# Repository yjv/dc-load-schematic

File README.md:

View this project on [CADLAB.io](https://cadlab.io/project/28803). 

# dc-load-schematic

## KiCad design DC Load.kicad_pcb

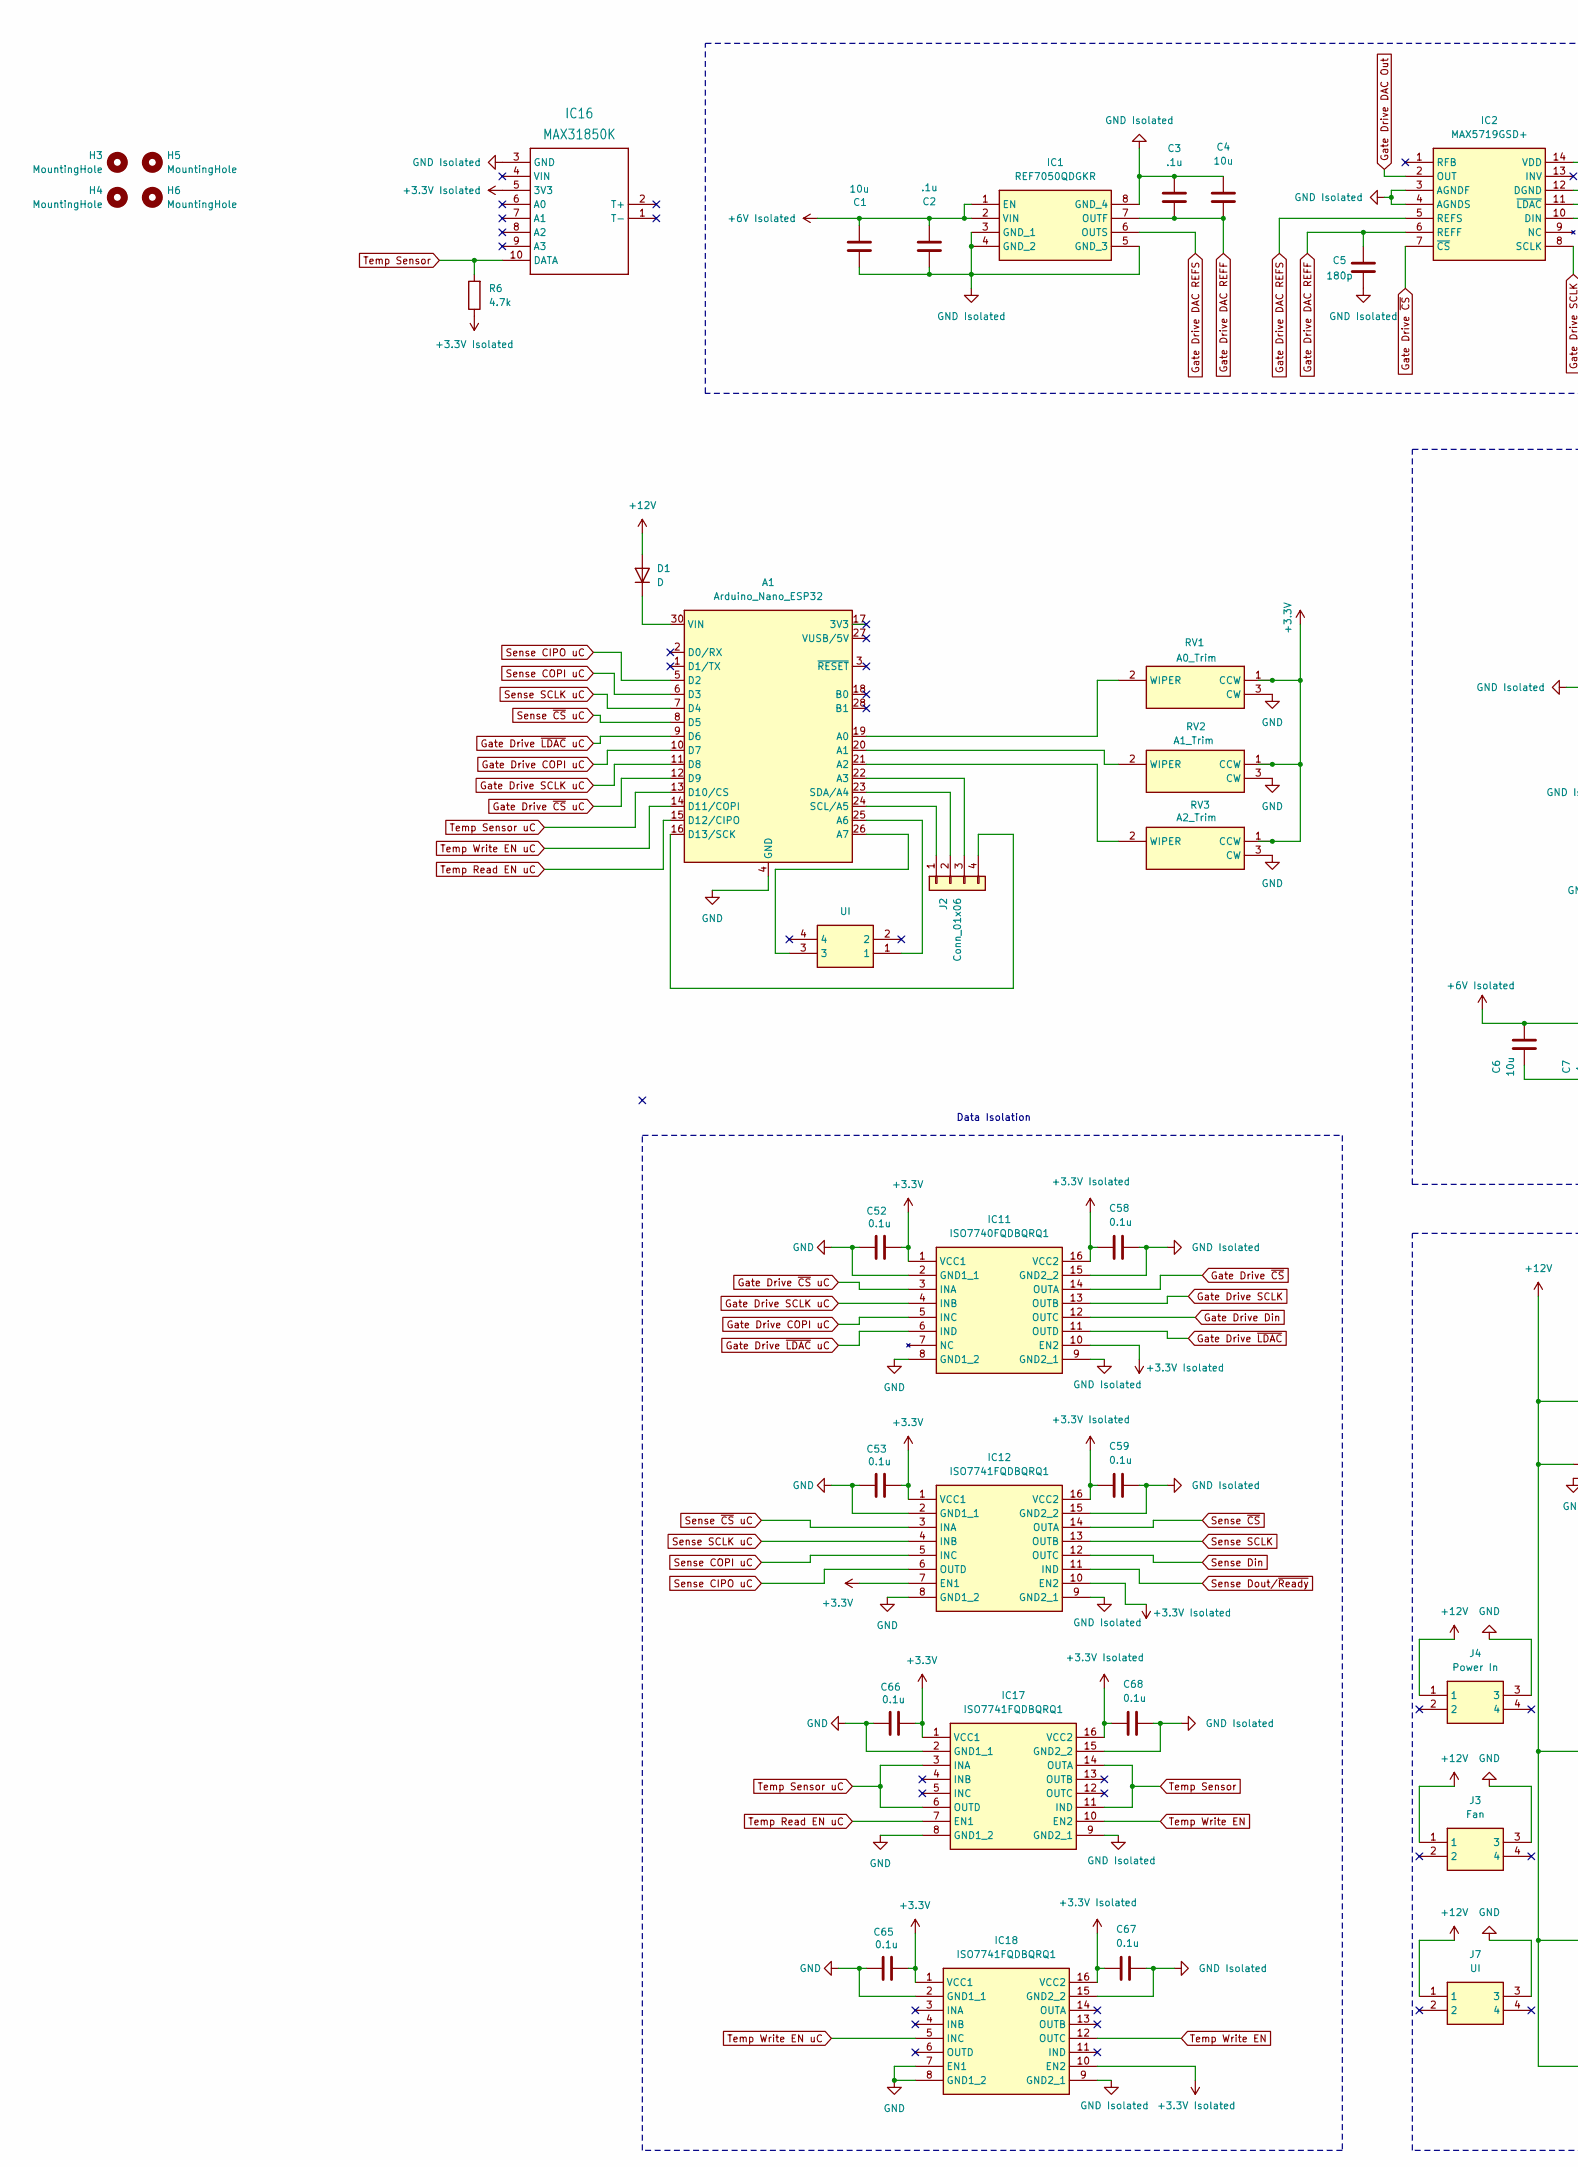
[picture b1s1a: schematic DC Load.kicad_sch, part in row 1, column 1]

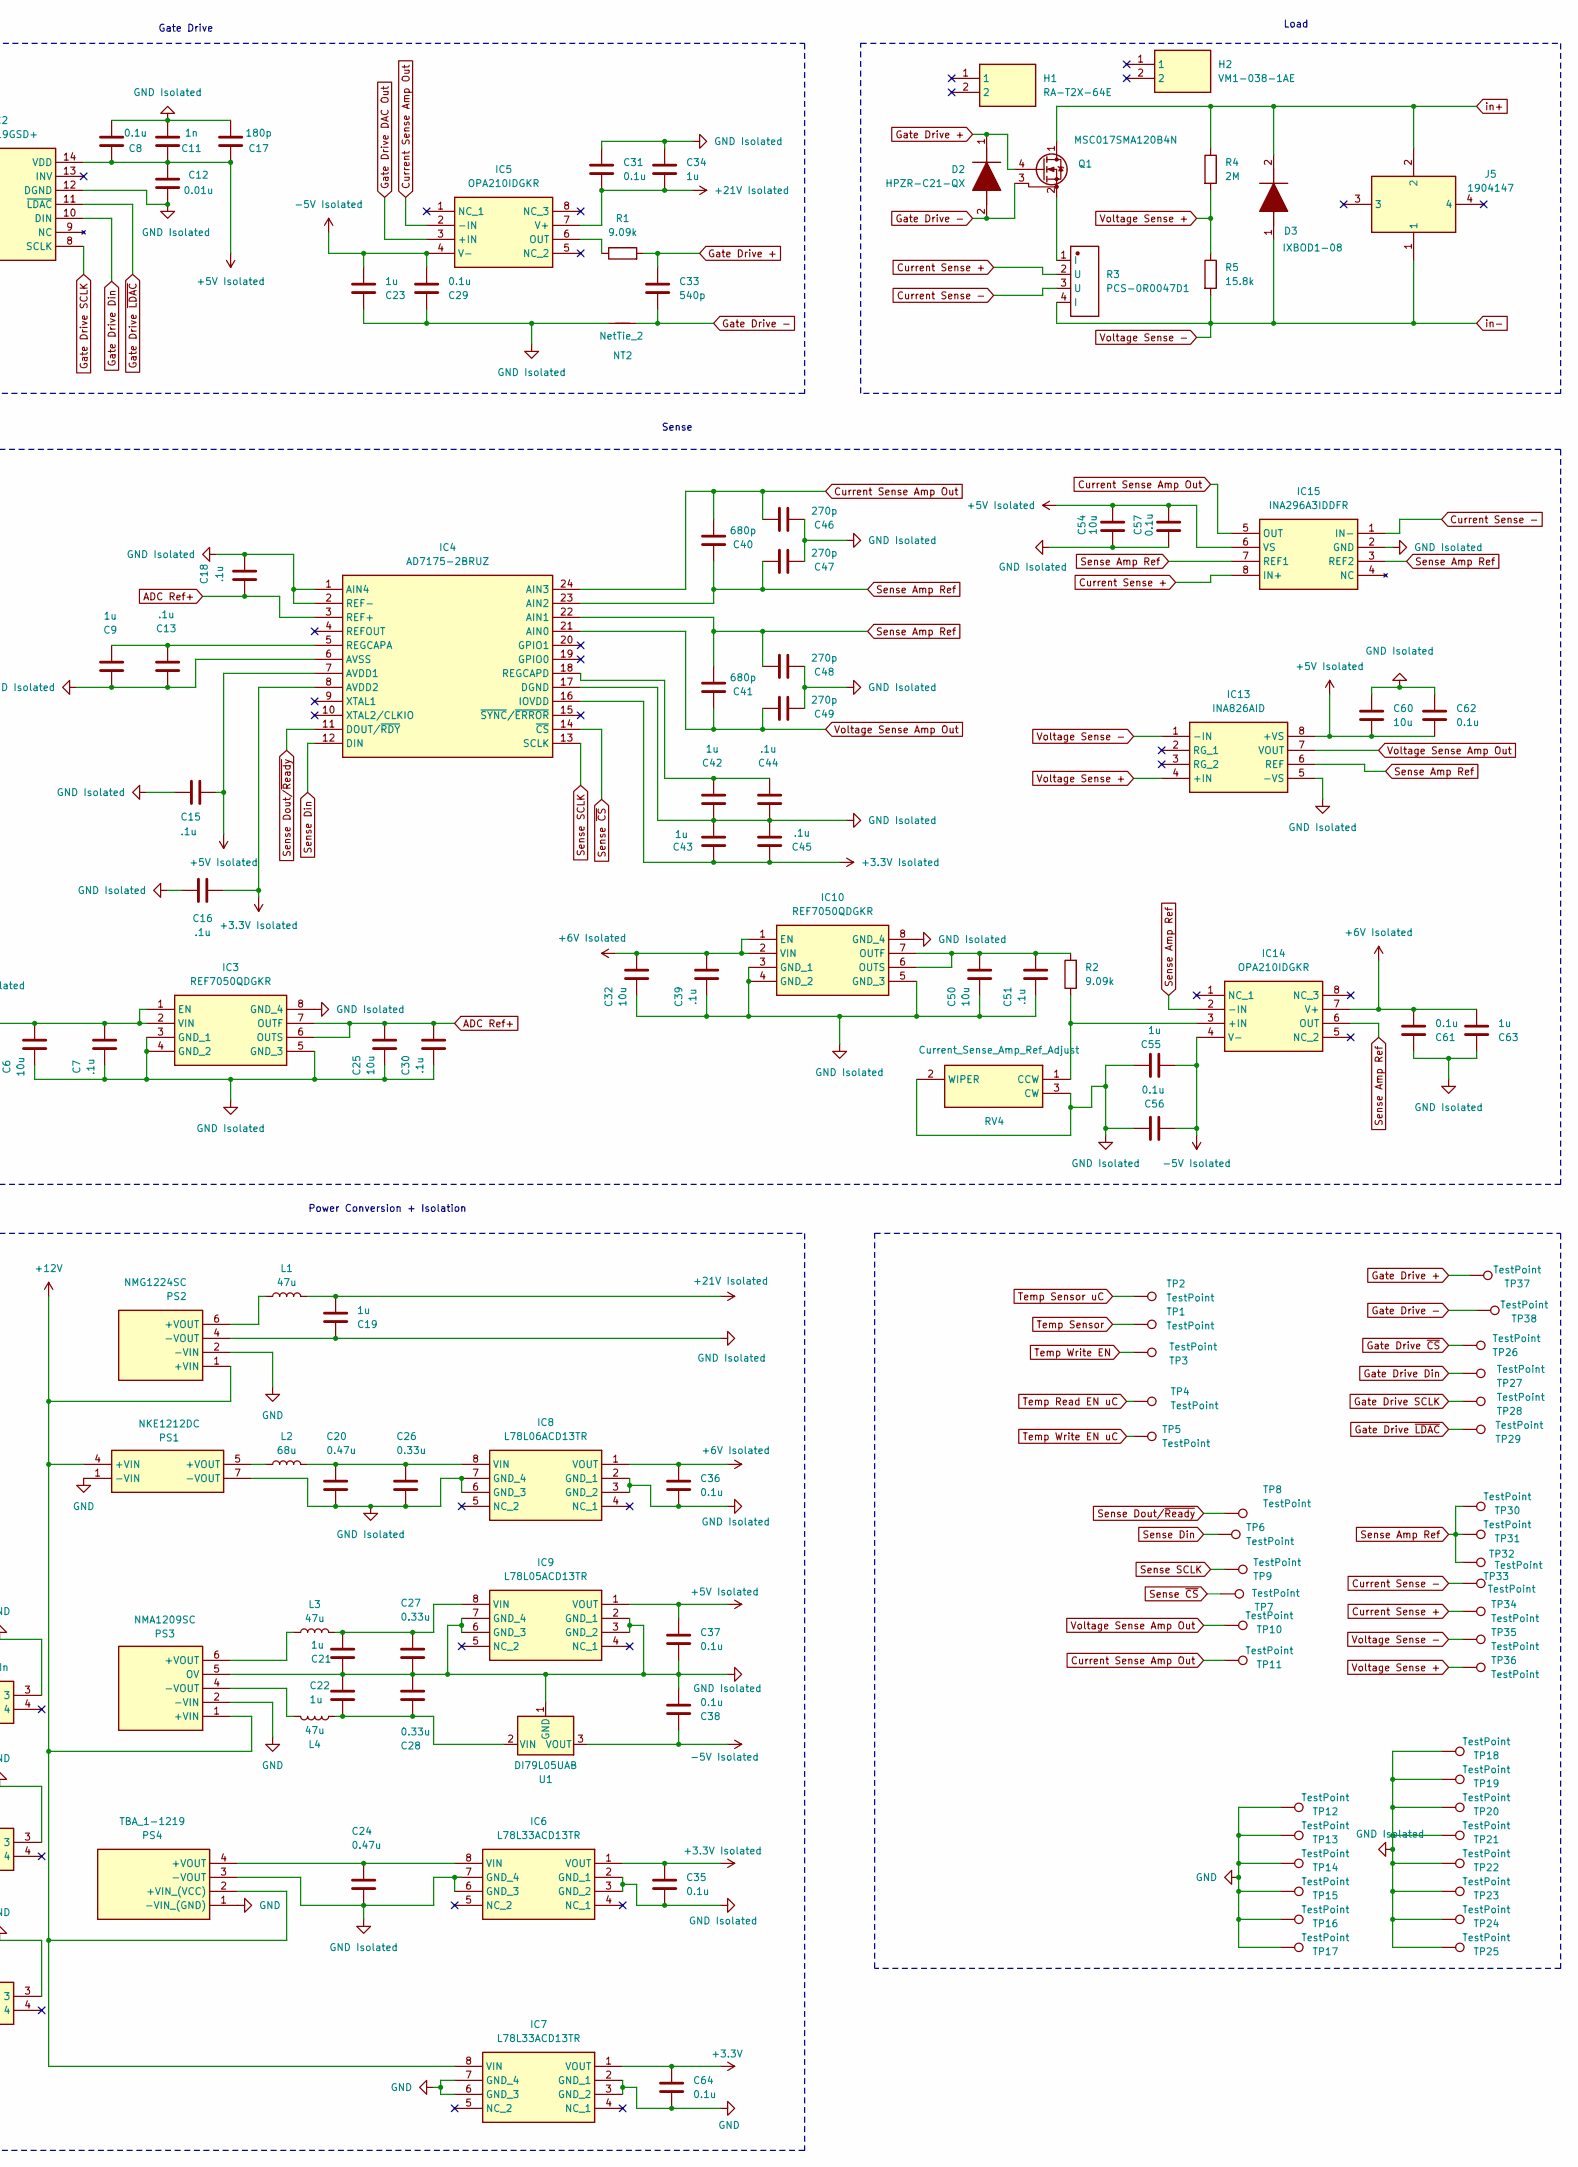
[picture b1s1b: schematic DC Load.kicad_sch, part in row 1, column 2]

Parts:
A1: Arduino_Nano_ESP32; Arduino_Nano
C1, C4, C6, C25, C32, C50, C54, C60: 10u; C_0805_2012Metric
C2, C3, C7, C13, C15, C16, C18, C30, C39, C44, C45, C51: .1u; C_0603_1608Metric
C5, C17: 180p; C_0805_2012Metric
C8, C35, C36, C37, C38, C52, C53, C56, C57, C58, C59, C61, C62, C64, C65, C66, C67, C68: 0.1u; C_0603_1608Metric
C9, C19, C21, C22, C23, C34, C42, C43, C55, C63: 1u; C_1206_3216Metric
C11: 1n; C_0603_1608Metric
C12: 0.01u; C_0805_2012Metric
C20, C24: 0.47u; C_0805_2012Metric
C26, C27, C28: 0.33u; C_0805_2012Metric
C29, C31: 0.1u; C_0805_2012Metric
C33: 540p; C_1210_3225Metric
C40, C41: 680p; C_0603_1608Metric
C46, C47, C48, C49: 270p; C_0603_1608Metric
D1: D; DIOM5336X245N
D2: HPZR-C21-QX; HPZRC21QX; Mouser Part Number 771-HPZR-C21-QX
D3: IXBOD1-08; IXBOD108; Mouser Part Number 747-IXBOD1-08
H1: RA-T2X-64E; RAT2X64E; Manufacturer_Part_Number RA-T2X-64E; Mouser Part Number 588-RA-T2X-64E
H2: VM1-038-1AE; Manufacturer_Part_Number RA-T2X-64E; Mouser Part Number 588-RA-T2X-64E
H3, H4, H5, H6: MountingHole; MountingHole_3.2mm_M3
IC1, IC3, IC10: REF7050QDGKR; SOP65P490X110-8N; Manufacturer_Part_Number REF7050QDGKR
IC2: MAX5719GSD+; SOIC127P600X175-14N; Mouser Part Number 700-MAX5719GSD+
IC4: AD7175-2BRUZ; SOP65P640X120-24N; Mouser Part Number 584-AD7175-2BRUZ
IC5, IC14: OPA210IDGKR; SOP65P490X110-8N; Mouser Part Number 595-OPA210IDGKR
IC6, IC7: L78L33ACD13TR; SOIC127P600X175-8N; Mouser Part Number 511-L78L33ACD-TR
IC8: L78L06ACD13TR; SOIC127P600X175-8N; Mouser Part Number 511-L78L06ACD-TR
IC9: L78L05ACD13TR; SOIC127P600X175-8N; Mouser Part Number 511-L78L05ACD-TR
IC11: ISO7740FQDBQRQ1; SOP64P600X175-16N; Mouser Part Number 595-ISO7740FQDBQRQ1
IC12, IC17, IC18: ISO7741FQDBQRQ1; SOP64P600X175-16N; Mouser Part Number 595-ISO7741FQDBQRQ1
IC13: INA826AID; SOIC127P600X175-8N; Mouser Part Number 595-INA826AID
IC15: INA296A3IDDFR; SOT65P280X110-8N; Mouser Part Number 595-INA296A3IDDFR
IC16: MAX31850K
J1, J7: UI; 1190363; Mouser Part Number 651-1190363
J2: Conn_01x06; PinSocket_1x04_P2.54mm_Vertical
J3: Fan; 1190363; Mouser Part Number 651-1190363
J4: Power In; 1190363; Mouser Part Number 651-1190363
J5: 1904147; Mouser Part Number 651-1904147
L1, L3, L4: 47u; 11R473C
L2: 68u; 11R683C
NT2: NetTie_2; NetTie-2_SMD_Pad2.0mm
PS1: NKE1212DC; NKE0503DC; Mouser Part Number 580-NKE1212DC
PS2: NMG1224SC; NMG0524SC; Mouser Part Number 580-NMG1224SC
PS3: NMA1209SC; Mouser Part Number 580-NMA1209SC
PS4: TBA_1-1219; TBA1; Mouser Part Number 495-TBA1-1219
Q1: MSC017SMA120B4N; TO-247-4_Vertical
R1, R2: 9.09k; R_1206_3216Metric
R3: PCS-0R0047D1; RES-TH_L22.3-W4.5-P7.62-L; Manufacturer Part PCS-0R0047D1
R4: 2M; R_2512_6332Metric
R5: 15.8k; R_0805_2012Metric
R6: 4.7k; R_1206_3216Metric
RV1: A0_Trim; 3386G1503LF; Mouser Part Number 652-3386G-1-472LF
RV2: A1_Trim; 3386G1503LF; Mouser Part Number 652-3386G-1-472LF
RV3: A2_Trim; 3386G1503LF; Mouser Part Number 652-3386G-1-472LF
RV4: Current_Sense_Amp_Ref_Adjust; 3386G1503LF; Mouser Part Number 652-3386G-1-472LF
TP1, TP2, TP3, TP4, TP5, TP6, TP7, TP8, TP9, TP10, TP11, TP26, TP27, TP28, TP29, TP30, TP31, TP32, TP33, TP34, TP35, TP36, TP37, TP38: TestPoint; TestPoint_Pad_SMD-0603
TP12, TP13, TP14, TP15, TP16, TP17, TP18, TP19, TP20, TP21, TP22, TP23, TP24, TP25: TestPoint; TestPoint_Keystone_5010-5014_Multipurpose
U1: DI79L05UAB; SOT-89-3

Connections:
+3.3V: C52.1, C53.1, C64.2, C65.1, C66.1, IC7.1 (VOUT), IC11.1 (VCC1), IC12.1 (VCC1), IC12.7 (EN1), IC17.1 (VCC1), IC18.1 (VCC1), RV1.1 (CCW), RV2.1 (CCW), RV3.1 (CCW)
+3.3V Isolated: C16.1, C35.2, C43.1, C45.1, C58.1, C59.1, C67.1, C68.1, IC4.8 (AVDD2), IC4.16 (IOVDD), IC6.1 (VOUT), IC11.10 (EN2), IC11.16 (VCC2), IC12.10 (EN2), IC12.16 (VCC2), IC16.5 (3V3), IC17.16 (VCC2), IC18.10 (EN2), IC18.16 (VCC2), R6.1
+5V Isolated: C8.1, C11.1, C12.1, C15.1, C17.1, C37.2, C54.2, C57.2, C60.2, C62.2, IC2.14 (VDD), IC4.7 (AVDD1), IC9.1 (VOUT), IC13.8 (+VS), IC15.6 (VS)
+6V Isolated: C1.2, C2.2, C6.2, C7.2, C32.2, C36.2, C39.2, C61.2, C63.2, IC1.1 (EN), IC1.2 (VIN), IC3.1 (EN), IC3.2 (VIN), IC8.1 (VOUT), IC10.1 (EN), IC10.2 (VIN), IC14.7 (V+)
+12V: D1.2 (A), IC7.8 (VIN), J3.1, J4.1, J7.1, PS1.4 (+VIN), PS2.1 (+VIN), PS3.1 (+VIN), PS4.2 (+VIN_(VCC))
+21V Isolated: C19.2, C31.2, C34.2, IC5.7 (V+), L1.1
-5V Isolated: C23.2, C29.2, C38.2, C55.2, C56.2, IC5.4 (V-), IC14.4 (V-), U1.3 (VOUT)
ADC Ref+: C18.1, C25.2, C30.2, IC3.6 (OUTS), IC3.7 (OUTF), IC4.3 (REF+)
Current Sense +: IC15.8 (IN+), R3.2 (U), TP34.1
Current Sense -: IC15.1 (IN-), R3.3 (U), TP33.1
Current Sense Amp Out: C40.2, C46.1, IC4.24 (AIN3), IC5.2 (-IN), IC15.5 (OUT), TP11.1
GND: A1.4 (GND), A1.29 (GND), C52.2, C53.2, C64.1, C65.2, C66.2, IC7.2 (GND_1), IC7.3 (GND_2), IC7.6 (GND_3), IC7.7 (GND_4), IC11.2 (GND1_1), IC11.8 (GND1_2), IC12.2 (GND1_1), IC12.8 (GND1_2), IC17.2 (GND1_1), IC17.8 (GND1_2), IC18.2 (GND1_1), IC18.7 (EN1), IC18.8 (GND1_2), J3.3, J4.3, J7.3, PS1.1 (-VIN), PS2.2 (-VIN), PS3.2 (-VIN), PS4.1 (-VIN_(GND)), RV1.3 (CW), RV2.3 (CW), RV3.3 (CW), TP12.1, TP13.1, TP14.1, TP15.1, TP16.1, TP17.1
GND Isolated: C1.1, C2.1, C3.1, C4.1, C5.2, C6.1, C7.1, C8.2, C9.1, C11.2, C12.2, C13.1, C15.2, C16.2, C17.2, C18.2, C19.1, C20.1, C21.1, C22.1, C23.1, C24.1, C25.1, C26.1, C27.1, C28.1, C29.1, C30.1, C31.1, C32.1, C34.1, C35.1, C36.1, C37.1, C38.1, C39.1, C42.1, C43.2, C44.1, C45.2, C46.2, C47.2, C48.2, C49.2, C50.1, C51.1, C54.1, C55.1, C56.1, C57.1, C58.2, C59.2, C60.1, C61.1, C62.1, C63.1, C67.2, C68.2, IC1.3 (GND_1), IC1.4 (GND_2), IC1.5 (GND_3), IC1.8 (GND_4), IC2.3 (AGNDF), IC2.4 (AGNDS), IC2.12 (DGND), IC3.3 (GND_1), IC3.4 (GND_2), IC3.5 (GND_3), IC3.8 (GND_4), IC4.1 (AIN4), IC4.2 (REF-), IC4.6 (AVSS), IC4.17 (DGND), IC6.2 (GND_1), IC6.3 (GND_2), IC6.6 (GND_3), IC6.7 (GND_4), IC8.2 (GND_1), IC8.3 (GND_2), IC8.6 (GND_3), IC8.7 (GND_4), IC9.2 (GND_1), IC9.3 (GND_2), IC9.6 (GND_3), IC9.7 (GND_4), IC10.3 (GND_1), IC10.4 (GND_2), IC10.5 (GND_3), IC10.8 (GND_4), IC11.9 (GND2_1), IC11.15 (GND2_2), IC12.9 (GND2_1), IC12.15 (GND2_2), IC13.5 (-VS), IC15.2 (GND), IC16.3 (GND), IC17.9 (GND2_1), IC17.15 (GND2_2), IC18.9 (GND2_1), IC18.15 (GND2_2), NT2.1, PS1.7 (-VOUT), PS2.4 (-VOUT), PS3.5 (OV), PS4.3 (-VOUT), RV4.2 (WIPER), RV4.3 (CW), TP18.1, TP19.1, TP20.1, TP21.1, TP22.1, TP23.1, TP24.1, TP25.1, U1.1 (GND)
Gate Drive +: C33.2, D2.1 (K), Q1.4 (G), R1.2, TP37.1
Gate Drive -: C33.1, D2.2 (A), NT2.2, Q1.3 (DS), TP38.1
Gate Drive COPI uC: A1.10 (D7), IC11.5 (INC)
Gate Drive DAC Out: IC2.2 (OUT), IC5.3 (+IN)
Gate Drive DAC REFF: C3.2, C4.2, C5.1, IC1.7 (OUTF), IC2.6 (REFF)
Gate Drive DAC REFS: IC1.6 (OUTS), IC2.5 (REFS)
Gate Drive Din: IC2.10 (DIN), IC11.12 (OUTC), TP27.1
Gate Drive SCLK: IC2.8 (SCLK), IC11.13 (OUTB), TP28.1
Gate Drive SCLK uC: A1.11 (D8), IC11.4 (INB)
Gate Drive ~CS: IC2.7 (~CS), IC11.14 (OUTA), TP26.1
Gate Drive ~CS uC: A1.12 (D9), IC11.3 (INA)
Gate Drive ~LDAC: IC2.11 (~LDAC), IC11.11 (OUTD), TP29.1
Gate Drive ~LDAC uC: A1.9 (D6), IC11.6 (IND)
unnamed: A1.19 (A0), RV1.2 (WIPER)
unnamed: A1.20 (A1), RV2.2 (WIPER)
unnamed: A1.21 (A2), RV3.2 (WIPER)
unnamed: A1.22 (A3), J2.3
unnamed: A1.25 (A6), J1.1
unnamed: A1.26 (A7), J1.3
unnamed: A1.16 (D13/SCK), J2.4
unnamed: A1.24 (SCL/A5), J2.1
unnamed: A1.23 (SDA/A4), J2.2
unnamed: A1.30 (VIN), D1.1 (K)
unnamed: C9.2, C13.2, IC4.5 (REGCAPA)
unnamed: C42.2, C44.2, IC4.18 (REGCAPD)
unnamed: IC5.6 (OUT), R1.1
unnamed: C24.2, IC6.8 (VIN), PS4.4 (+VOUT)
unnamed: C20.2, C26.2, IC8.8 (VIN), L2.1
unnamed: C21.2, C27.2, IC9.8 (VIN), L3.1
unnamed: C50.2, C51.2, IC10.6 (OUTS), IC10.7 (OUTF), R2.2
unnamed: IC14.3 (+IN), R2.1, RV4.1 (CCW)
unnamed: L2.2, PS1.5 (+VOUT)
unnamed: L1.2, PS2.6 (+VOUT)
unnamed: L3.2, PS3.6 (+VOUT)
unnamed: L4.2, PS3.4 (-VOUT)
unnamed: Q1.2 (S), R3.1 (I)
unnamed: C22.2, C28.2, L4.1, U1.2 (VIN)
Sense Amp Ref: C40.1, C41.2, C47.1, C48.1, IC4.22 (AIN1), IC4.23 (AIN2), IC13.6 (REF), IC14.2 (-IN), IC14.6 (OUT), IC15.3 (REF2), IC15.7 (REF1), TP30.1, TP31.1, TP32.1
Sense CIPO uC: A1.5 (D2), IC12.6 (OUTD)
Sense COPI uC: A1.6 (D3), IC12.5 (INC)
Sense Din: IC4.12 (DIN), IC12.12 (OUTC), TP6.1
Sense Dout/~Ready: IC4.11 (DOUT/~RDY), IC12.11 (IND), TP8.1
Sense SCLK: IC4.13 (SCLK), IC12.13 (OUTB), TP9.1
Sense SCLK uC: A1.7 (D4), IC12.4 (INB)
Sense ~CS: IC4.14 (~CS), IC12.14 (OUTA), TP7.1
Sense ~CS uC: A1.8 (D5), IC12.3 (INA)
Temp Read EN uC: A1.15 (D12/CIPO), IC17.7 (EN1), TP4.1
Temp Sensor: IC16.10 (DATA), IC17.11 (IND), IC17.14 (OUTA), R6.2, TP1.1
Temp Sensor uC: A1.13 (D10/CS), IC17.3 (INA), IC17.6 (OUTD), TP2.1
Temp Write EN: IC17.10 (EN2), IC18.12 (OUTC), TP3.1
Temp Write EN uC: A1.14 (D11/COPI), IC18.5 (INC), TP5.1
Voltage Sense +: IC13.4 (+IN), R4.2, R5.1, TP36.1
Voltage Sense -: D3.1 (A), IC13.1 (-IN), J5.1, R3.4 (I), R5.2, TP35.1
Voltage Sense Amp Out: C41.1, C49.1, IC4.21 (AIN0), IC13.7 (VOUT), TP10.1
in+: D3.2 (K), J5.2, Q1.1 (D), R4.1

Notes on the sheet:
Gate Drive
Sense
Power Conversion + Isolation
Load
Data Isolation

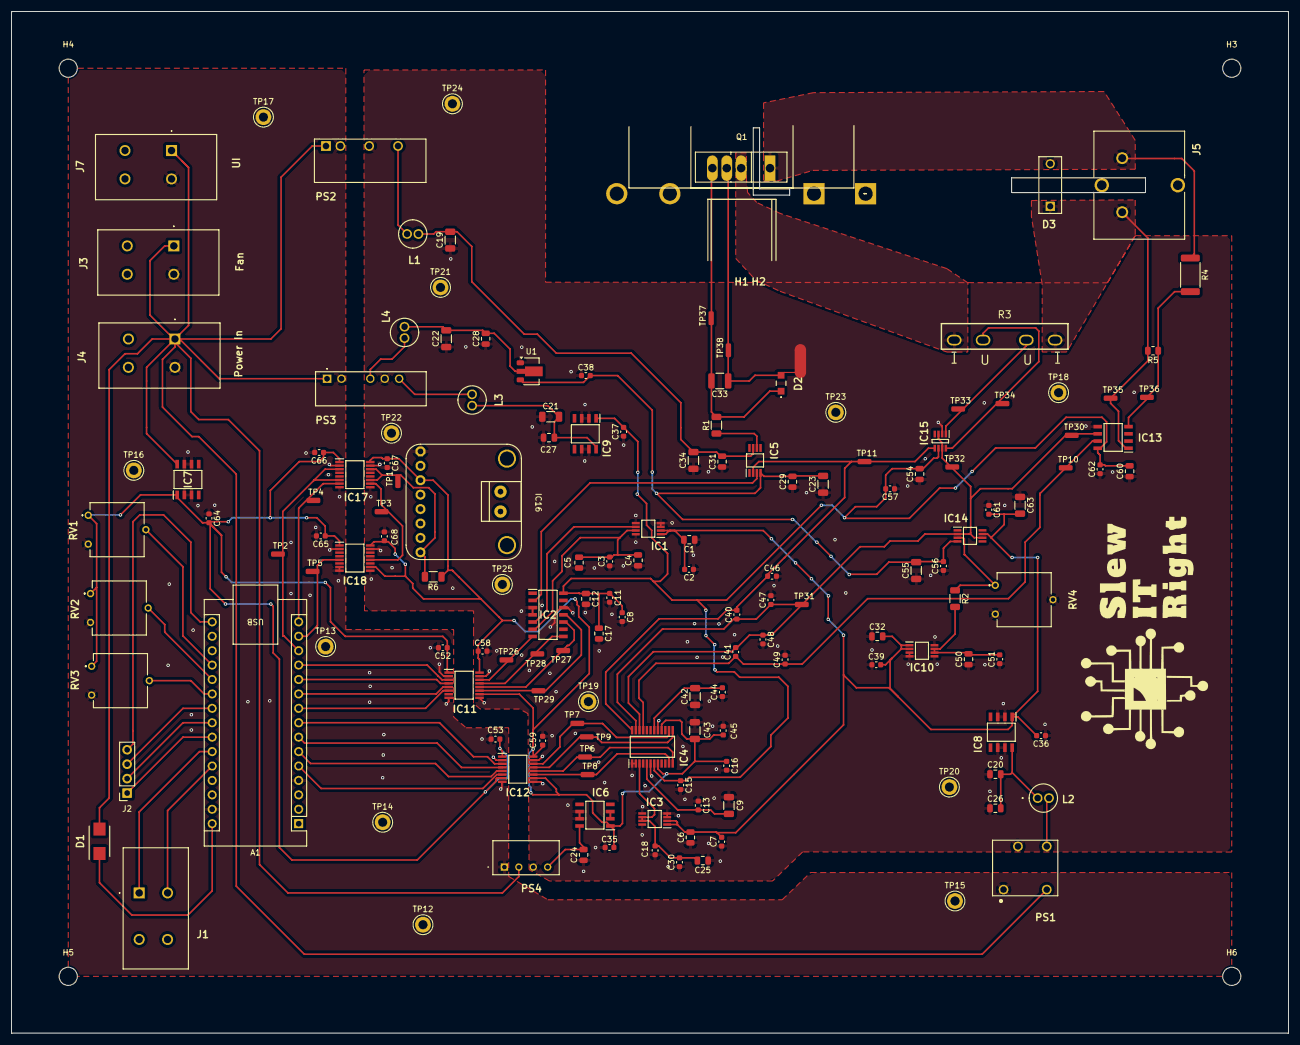
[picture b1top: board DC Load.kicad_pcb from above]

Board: 2 copper layers, 225.0 x 180.0 mm, 159 parts (0 on the bottom side), 68 nets.

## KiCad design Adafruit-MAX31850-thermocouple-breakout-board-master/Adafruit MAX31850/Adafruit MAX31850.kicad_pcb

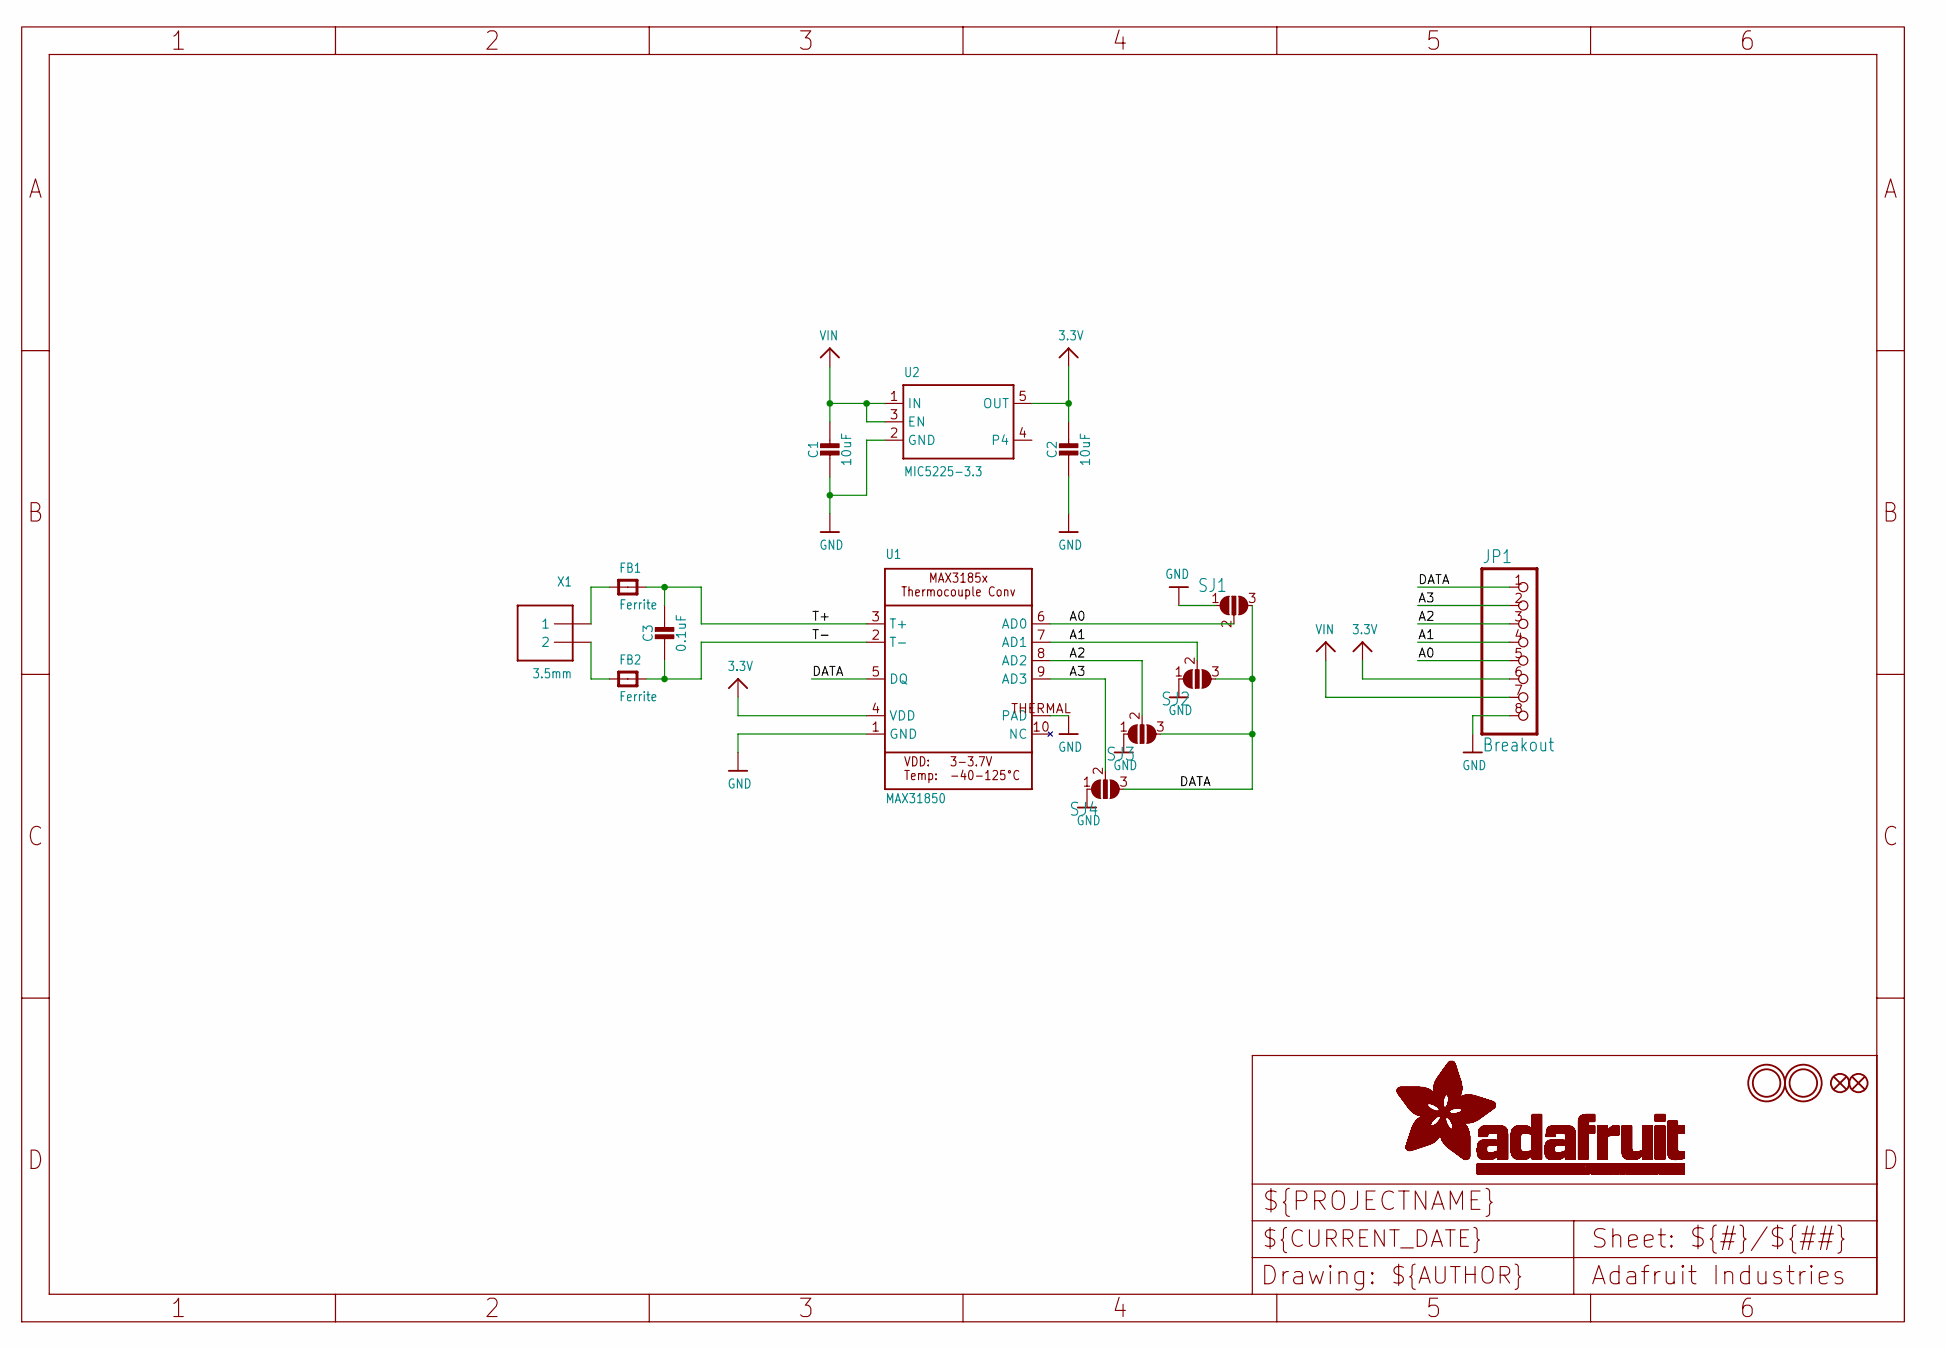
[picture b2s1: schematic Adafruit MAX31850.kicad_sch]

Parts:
C1, C2: 10uF; 0805-NO
C3: 0.1uF; 0805-NO
FB1, FB2: Ferrite; 0805
FID1, FID2: FIDUCIAL""; FIDUCIAL_1MM
JP1: Breakout; 1X08_ROUND_70
SJ1, SJ2, SJ3, SJ4: SOLDERJUMPER_2WAY; SOLDERJUMPER_2WAY_OPEN_NOPASTE
U1: MAX31850; TDFN10_3X4MM
U2: MIC5225-3.3; SOT23-5
U$8, U$9: MOUNTINGHOLE2.5; MOUNTINGHOLE_2.5_PLATED
X1: 3.5mm; TERMBLOCK_1X2-3.5MM

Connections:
3.3V: C2.1, JP1.6, U1.4 (VDD), U2.5 (OUT)
A0: JP1.5, SJ1.2, U1.6 (AD0)
A1: JP1.4, SJ2.2, U1.7 (AD1)
A2: JP1.3, SJ3.2, U1.8 (AD2)
A3: JP1.2, SJ4.2, U1.9 (AD3)
DATA: JP1.1, SJ1.3, SJ2.3, SJ3.3, SJ4.3, U1.5 (DQ)
GND: C1.2, C2.2, JP1.8, SJ1.1, SJ2.1, SJ3.1, SJ4.1, U1.1 (GND), U1.THERMAL (PAD), U2.2 (GND)
unnamed: FB1.1, X1.1
unnamed: FB2.1, X1.2
T+: C3.1, FB1.2, U1.3 (T+)
T-: C3.2, FB2.2, U1.2 (T-)
VIN: C1.1, JP1.7, U2.1 (IN), U2.3 (EN)

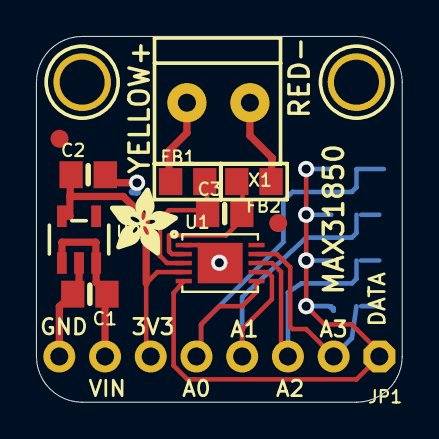
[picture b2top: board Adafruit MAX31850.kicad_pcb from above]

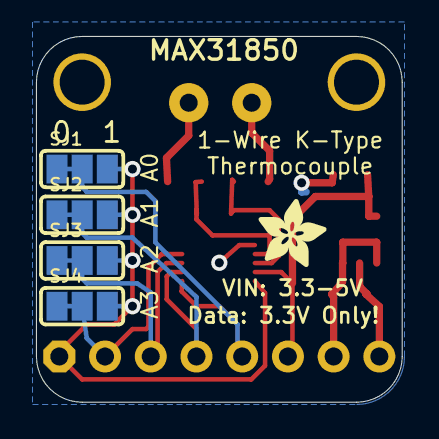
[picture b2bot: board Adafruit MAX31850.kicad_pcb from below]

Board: 2 copper layers, 20.3 x 20.3 mm, 19 parts (5 on the bottom side), 12 nets.

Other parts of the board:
U$18, U$19: ADAFRUIT_3.5MM

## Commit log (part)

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2025-01-27 Iinitial Commit
2025-01-27 Backlink to CADLAB.io has been added.
2025-01-27 Started putting together the full circuit
2025-02-25 Updated the schematic for the control loop
2025-03-30 Got the PCB layed out exlucing the grounds
2025-04-01 Finished laying out all the traces and adding the temperature sensing circuitry
2025-04-02 Added pdf printouts of the PCB and schematic
2025-04-02 improved the connection to the temp sensor
2025-04-03 added test points
2025-04-03 added mounting holes
2025-04-03 added 3D models
2025-04-03 added the rest of the 3D models. Added logo
2025-04-23 small changes
2025-06-05 fixed net names for DAC communincation
2025-07-18 Improvements
